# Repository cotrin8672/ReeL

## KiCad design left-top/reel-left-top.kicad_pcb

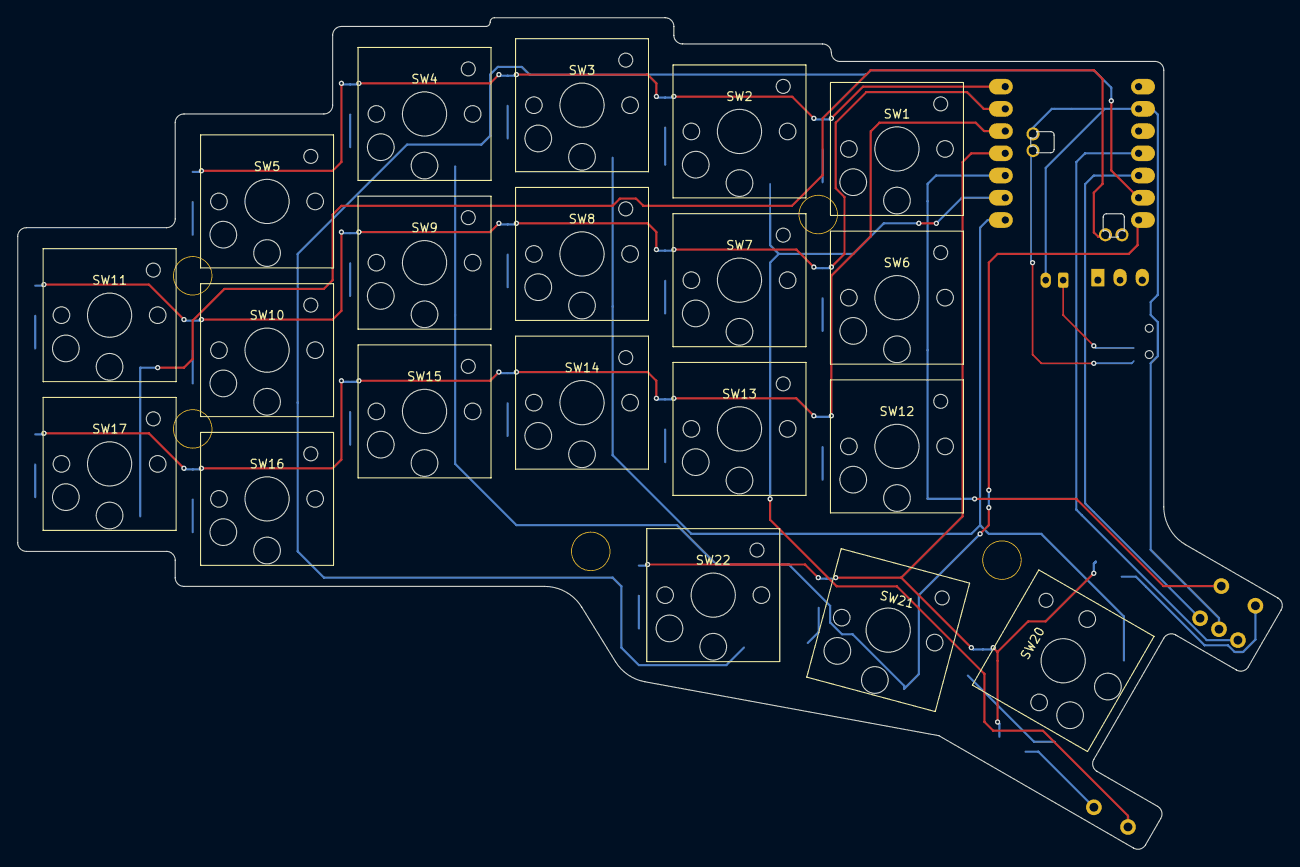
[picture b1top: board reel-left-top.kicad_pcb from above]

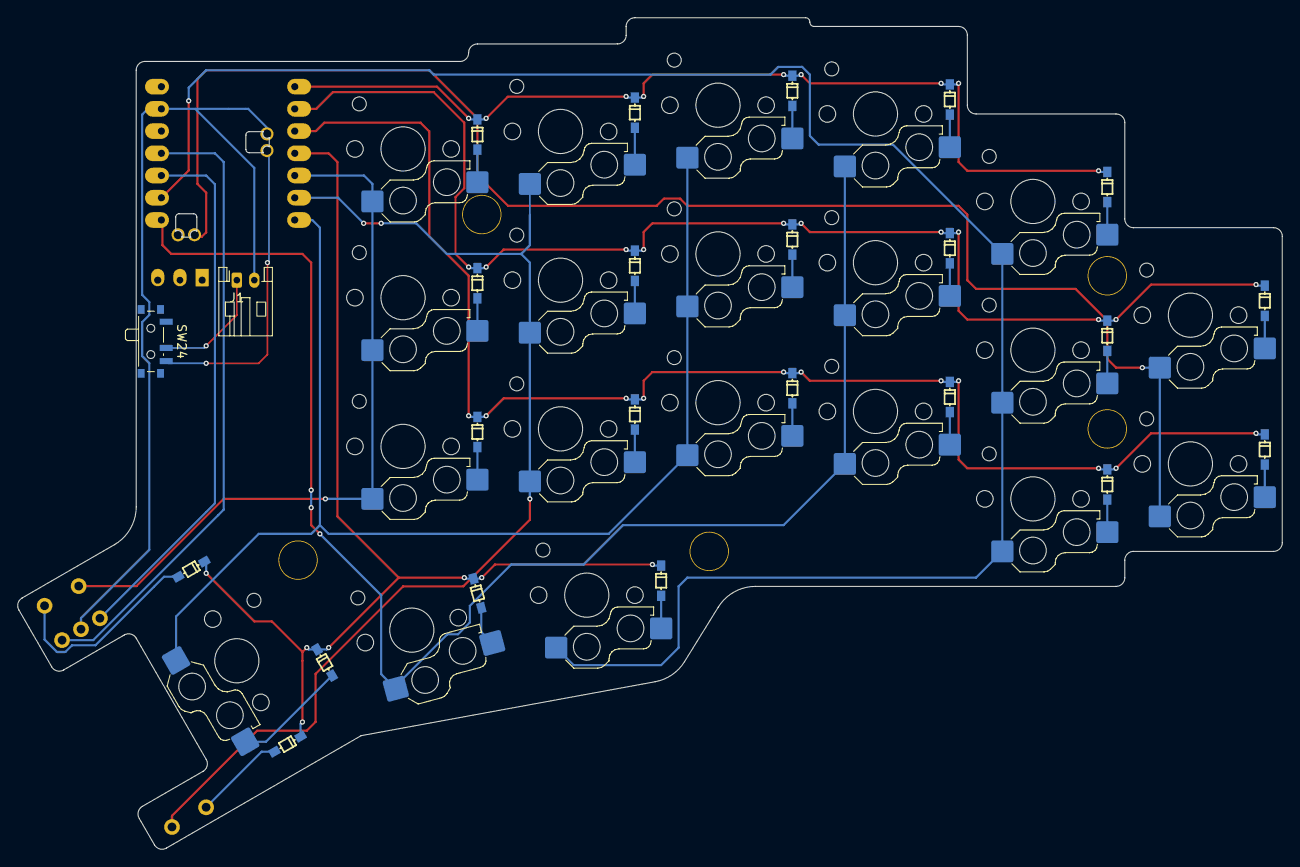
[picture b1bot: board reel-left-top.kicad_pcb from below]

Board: 2 copper layers, 144.5 x 95.0 mm, 53 parts (2 on the bottom side), 37 nets.

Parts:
D1, D2, D3, D4, D5, D6, D7, D8, D9, D10, D11, D12, D13, D14, D15, D16, D17, D18, D19, D20, D21, D22: D; Diode_SMD
J1: Conn_01x02; JST_PH_S2B-PH-K_1x02_P2.00mm_Horizontal
Ref**: Val**; m2_Spacer_Hole
Ref**#2, Ref**#3, Ref**#4, Ref**#5: Val**; m2_Spacer_Hole
SW1, SW2, SW3, SW4, SW5, SW6, SW7, SW8, SW9, SW10, SW11, SW12, SW13, SW14, SW15, SW16, SW17, SW20, SW21, SW22: SW_Push; SW_Hotswap_Kailh_Choc_V1V2_1.00u
SW18, SW19: SW_Push; SideTactSwitch_2pin
SW24: SW_SPDT; SW_SPDT_PCM12
SW25: RotaryEncoder; RotaryEncoder_BM10_3Pin
U1: XIAO_nRF52840_wBAT_wNFC_1

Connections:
Col0: SW1.1, SW6.1, SW12.1, SW18.1, U1.5 (P0.04_A4_D4_SDA)
Col1: SW2.1, SW7.1, SW13.1, SW19.1, U1.6 (P0.05_A5_D5_SCL)
Col2: SW3.1, SW8.1, SW14.1, SW20.1, U1.7 (P1.11_D6_TX)
Col3: SW4.1, SW9.1, SW15.1, SW21.1, U1.8 (P1.12_D7_RX)
Col4: SW5.1, SW10.1, SW16.1, SW22.1, U1.9 (P1.13_D8_SCK)
Col5: SW11.1, SW17.1, U1.15 (NFC1_0.09)
GND: J1.2, SW25.C, U1.13 (GND), U1.21 (BATT-)
unnamed: D1.2 (A), SW1.2
unnamed: D2.2 (A), SW2.2
unnamed: D3.2 (A), SW3.2
unnamed: D4.2 (A), SW4.2
unnamed: D5.2 (A), SW5.2
unnamed: D6.2 (A), SW6.2
unnamed: D7.2 (A), SW7.2
unnamed: D8.2 (A), SW8.2
unnamed: D9.2 (A), SW9.2
unnamed: D10.2 (A), SW10.2
unnamed: D11.2 (A), SW11.2
unnamed: D12.2 (A), SW12.2
unnamed: D13.2 (A), SW13.2
unnamed: D14.2 (A), SW14.2
unnamed: D15.2 (A), SW15.2
unnamed: D16.2 (A), SW16.2
unnamed: D17.2 (A), SW17.2
unnamed: D18.2 (A), SW18.2
unnamed: D19.2 (A), SW19.2
unnamed: D20.2 (A), SW20.2
unnamed: D21.2 (A), SW21.2
unnamed: D22.2 (A), SW22.2
unnamed: J1.1, SW24.2 (B)
RotA: SW25.A, U1.10 (P1.14_D9_MISO)
RotB: SW25.B, U1.11 (P1.15_D10_MOSI)
Row0: D1.1 (K), D2.1 (K), D3.1 (K), D4.1 (K), D5.1 (K), U1.1 (P0.02_A0_D0)
Row1: D6.1 (K), D7.1 (K), D8.1 (K), D9.1 (K), D10.1 (K), D11.1 (K), U1.2 (P0.03_A1_D1)
Row2: D12.1 (K), D13.1 (K), D14.1 (K), D15.1 (K), D16.1 (K), D17.1 (K), U1.3 (P0.28_A2_D2)
Row3: D18.1 (K), D19.1 (K), D20.1 (K), D21.1 (K), D22.1 (K), U1.4 (P0.29_A3_D3)
VBAT_SW: SW24.3 (C), U1.20 (BATT+)
